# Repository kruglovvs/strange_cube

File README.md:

# strange_game
Учебный проект аппаратно-программной разработки. Представляет собой несколько плат, собираемых в куб и с напаянными различными датчиками периферии, и плату esp32 с кодом, написанным на C# nanoframework

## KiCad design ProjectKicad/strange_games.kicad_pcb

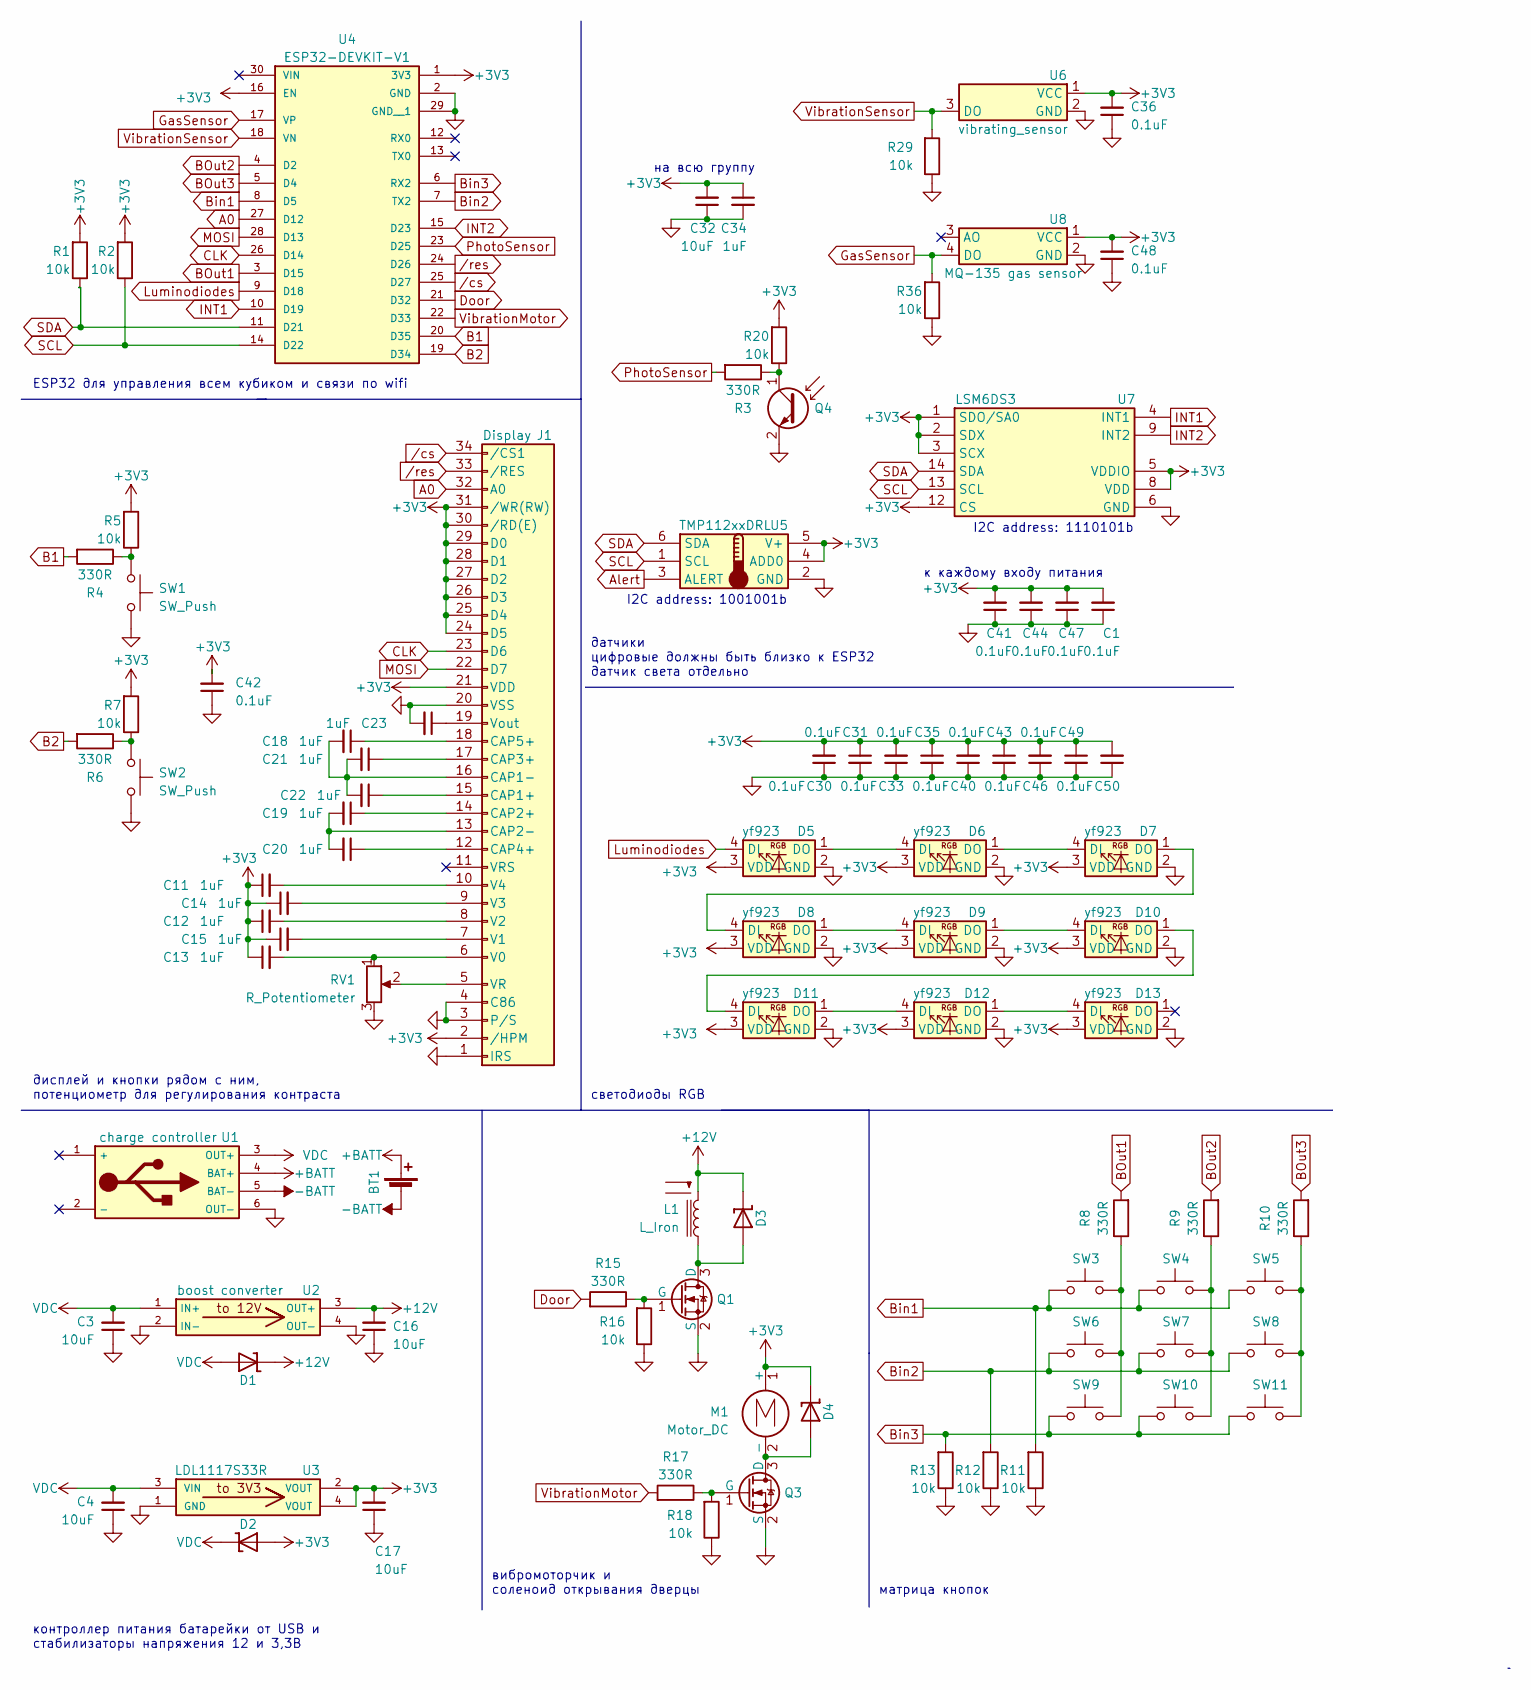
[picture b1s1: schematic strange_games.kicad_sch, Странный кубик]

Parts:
BT1: Battery_Cell; BatteryHolder_MPD_BH-18650-PC2
C1, C30, C31, C33, C35, C36, C40, C41, C42, C43, C44, C46, C47, C48, C49, C50: C_Generic; C_0402_1005Metric; Voltage 10V
C3, C4, C16, C17, C32: C_Generic; C_0805_2012Metric; Voltage 6.3V
C11, C12, C13, C14, C15, C18, C19, C20, C21, C22, C23, C34: C_Generic; C_0402_1005Metric; Voltage 16V
D1, D2, D3, D4: S07B-GS08; D_SMF
D5, D6, D7, D8, D9, D10, D11, D12, D13: yf923; library
J1: Display; TE_3-1734839-4_1x34-1MP_P0.5mm_Horizontal
L1: L_Iron; PinHeader_1x02_P2.54mm_Vertical
M1: Motor_DC; PinHeader_1x02_P2.54mm_Vertical
Q1, Q3: Si2302A; SOT-23-3; Part Number SI2318DS-T1-GE3; JLCPCB ID C14498
Q4: Q_Photo; LED_D4.0mm
R1, R2, R5, R7, R11, R12, R13, R16, R18, R20, R29, R36: 10k_0805; R_0805_2012Metric; Part Number RC0603FR-071K2L; JLCPCB ID C22765
R3, R4, R6, R8, R9, R10, R15, R17: 330_0805; R_0805_2012Metric; Part Number RC0603FR-071K2L; JLCPCB ID C22765
RV1: R_Potentiometer; TRIM_3362P-1-203LF
SW1, SW2, SW3, SW4, SW5, SW6, SW7, SW8, SW9, SW10, SW11: SW_Push; SW_PUSH-12mm
U1: charge controller; charge_controller_module_tp4056
U2: boost converter; CKCS BS-01 MT-3608 Boost Converter
U3: LDL1117S33R; SOT230P700X180-4N; Out voltage 3.3V; PARTREV 7
U4: ESP32-DEVKIT-V1; MODULE_ESP32_DEVKIT_V1; PARTREV N/A
U5: TMP112xxDRL; SOT-563
U6: vibrating_sensor; PinHeader_1x03_P2.54mm_Vertical
U7: LSM6DS3; LGA-14_3x2.5mm_P0.5mm_LayoutBorder3x4y
U8: MQ-135 gas sensor; PinHeader_1x04_P2.54mm_Vertical

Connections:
+3V3: C1.2, C11.1, C12.1, C13.1, C14.1, C15.1, C17.2, C30.2, C31.1, C32.2, C33.2, C34.1, C35.1, C36.2, C40.2, C41.2, C42.2, C43.1, C44.2, C46.2, C47.2, C48.2, C49.1, C50.2, D2.2 (A), D4.1 (K), D5.3 (VDD), D6.3 (VDD), D7.3 (VDD), D8.3 (VDD), D9.3 (VDD), D10.3 (VDD), D11.3 (VDD), D12.3 (VDD), D13.3 (VDD), J1.2 (/HPM), J1.21 (VDD), J1.24 (D5), J1.25 (D4), J1.26 (D3), J1.27 (D2), J1.28 (D1), J1.29 (D0), J1.30 (/RD(E)), J1.31 (/WR(RW)), M1.1 (+), R1.2, R2.2, R5.2, R7.2, R20.2, U3.2 (VOUT), U3.4 (VOUT), U4.1 (3V3), U4.16 (EN), U5.4 (ADD0), U5.5 (V+), U6.1 (VCC), U7.1 (SDO/SA0), U7.2 (SDX), U7.3 (SCX), U7.5 (VDDIO), U7.8 (VDD), U7.12 (CS), U8.1 (VCC)
+12V: C16.2, D1.1 (K), D3.1 (K), L1.1, U2.3 (OUT+)
+BATT: BT1.2 (+), U1.4 (BAT+)
-BATT: BT1.1 (-), U1.5 (BAT-)
A0: J1.32 (A0), U4.27 (D12)
Alert: U5.3 (ALERT)
B1: R4.2, U4.20 (D35)
B2: R6.2, U4.19 (D34)
BOut1: R8.2, U4.3 (D15)
BOut2: R9.2, U4.4 (D2)
BOut3: R10.2, U4.5 (D4)
Bin1: R11.2, SW3.1, SW4.1, SW5.1, U4.8 (D5)
Bin2: R12.2, SW6.1, SW7.1, SW8.1, U4.7 (TX2)
Bin3: R13.2, SW9.1, SW10.1, SW11.1, U4.6 (RX2)
CLK: J1.23 (D6), U4.26 (D14)
Door: R15.2, U4.21 (D32)
GND: C1.1, C3.1, C4.1, C16.1, C17.1, C23.2, C30.1, C31.2, C32.1, C33.1, C34.2, C35.2, C36.1, C40.1, C41.1, C42.1, C43.2, C44.1, C46.1, C47.1, C48.1, C49.2, C50.1, D5.2 (GND), D6.2 (GND), D7.2 (GND), D8.2 (GND), D9.2 (GND), D10.2 (GND), D11.2 (GND), D12.2 (GND), D13.2 (GND), J1.1 (IRS), J1.3 (P/S), J1.4 (C86), J1.20 (VSS), Q1.2 (S), Q3.2 (S), Q4.2 (E), R11.1, R12.1, R13.1, R16.1, R18.1, R29.1, R36.1, RV1.3, SW1.2, SW2.2, U1.6 (OUT-), U2.2 (IN-), U2.4 (OUT-), U3.1 (GND), U4.2 (GND), U4.29 (GND__1), U5.2 (GND), U6.2 (GND), U7.6 (GND), U7.7 (GND), U8.2 (GND)
GasSensor: R36.2, U4.17 (VP), U8.4 (DO)
INT1: U4.10 (D19), U7.4 (INT1)
INT2: U4.15 (D23), U7.9 (INT2)
Luminodiodes: D5.4 (DI), U4.9 (D18)
MOSI: J1.22 (D7), U4.28 (D13)
unnamed: D3.2 (A), L1.2, Q1.3 (D)
unnamed: D4.2 (A), M1.2 (-), Q3.3 (D)
unnamed: D5.1 (DO), D6.4 (DI)
unnamed: D6.1 (DO), D7.4 (DI)
unnamed: D7.1 (DO), D8.4 (DI)
unnamed: D8.1 (DO), D9.4 (DI)
unnamed: D9.1 (DO), D10.4 (DI)
unnamed: D10.1 (DO), D11.4 (DI)
unnamed: D11.1 (DO), D12.4 (DI)
unnamed: D12.1 (DO), D13.4 (DI)
unnamed: C22.1, J1.15 (CAP1+)
unnamed: C18.2, C21.2, C22.2, J1.16 (CAP1-)
unnamed: C19.1, J1.14 (CAP2+)
unnamed: C19.2, C20.2, J1.13 (CAP2-)
unnamed: C21.1, J1.17 (CAP3+)
unnamed: C20.1, J1.12 (CAP4+)
unnamed: C18.1, J1.18 (CAP5+)
unnamed: C13.2, J1.6 (V0), RV1.1
unnamed: C15.2, J1.7 (V1)
unnamed: C12.2, J1.8 (V2)
unnamed: C14.2, J1.9 (V3)
unnamed: C11.2, J1.10 (V4)
unnamed: J1.5 (VR), RV1.2
unnamed: C23.1, J1.19 (Vout)
unnamed: Q1.1 (G), R15.1, R16.2
unnamed: Q3.1 (G), R17.1, R18.2
unnamed: Q4.1 (C), R3.1, R20.1
unnamed: R4.1, R5.1, SW1.1
unnamed: R6.1, R7.1, SW2.1
unnamed: R8.1, SW3.2, SW6.2, SW9.2
unnamed: R9.1, SW4.2, SW7.2, SW10.2
unnamed: R10.1, SW5.2, SW8.2, SW11.2
PhotoSensor: R3.2, U4.23 (D25)
SCL: R2.1, U4.14 (D22), U5.1 (SCL), U7.13 (SCL)
SDA: R1.1, U4.11 (D21), U5.6 (SDA), U7.14 (SDA)
VDC: C3.2, C4.2, D1.2 (A), D2.1 (K), U1.3 (OUT+), U2.1 (IN+), U3.3 (VIN)
VibrationMotor: R17.2, U4.22 (D33)
VibrationSensor: R29.2, U4.18 (VN), U6.3 (DO)
/cs: J1.34 (/CS1), U4.25 (D27)
/res: J1.33 (/RES), U4.24 (D26)

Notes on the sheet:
к каждому входу питания
светодиоды RGB
ESP32 для управления всем кубиком и связи по wifi
матрица кнопок
вибромоторчик и соленоид открывания дверцы
дисплей и кнопки рядом с ним, потенциометр для регулирования контраста
на всю группу
I2C address: 1001001b
датчики цифровые должны быть близко к ESP32 датчик света отдельно
I2C address: 1110101b
контроллер питания батарейки от USB и стабилизаторы напряжения 12 и 3,3В

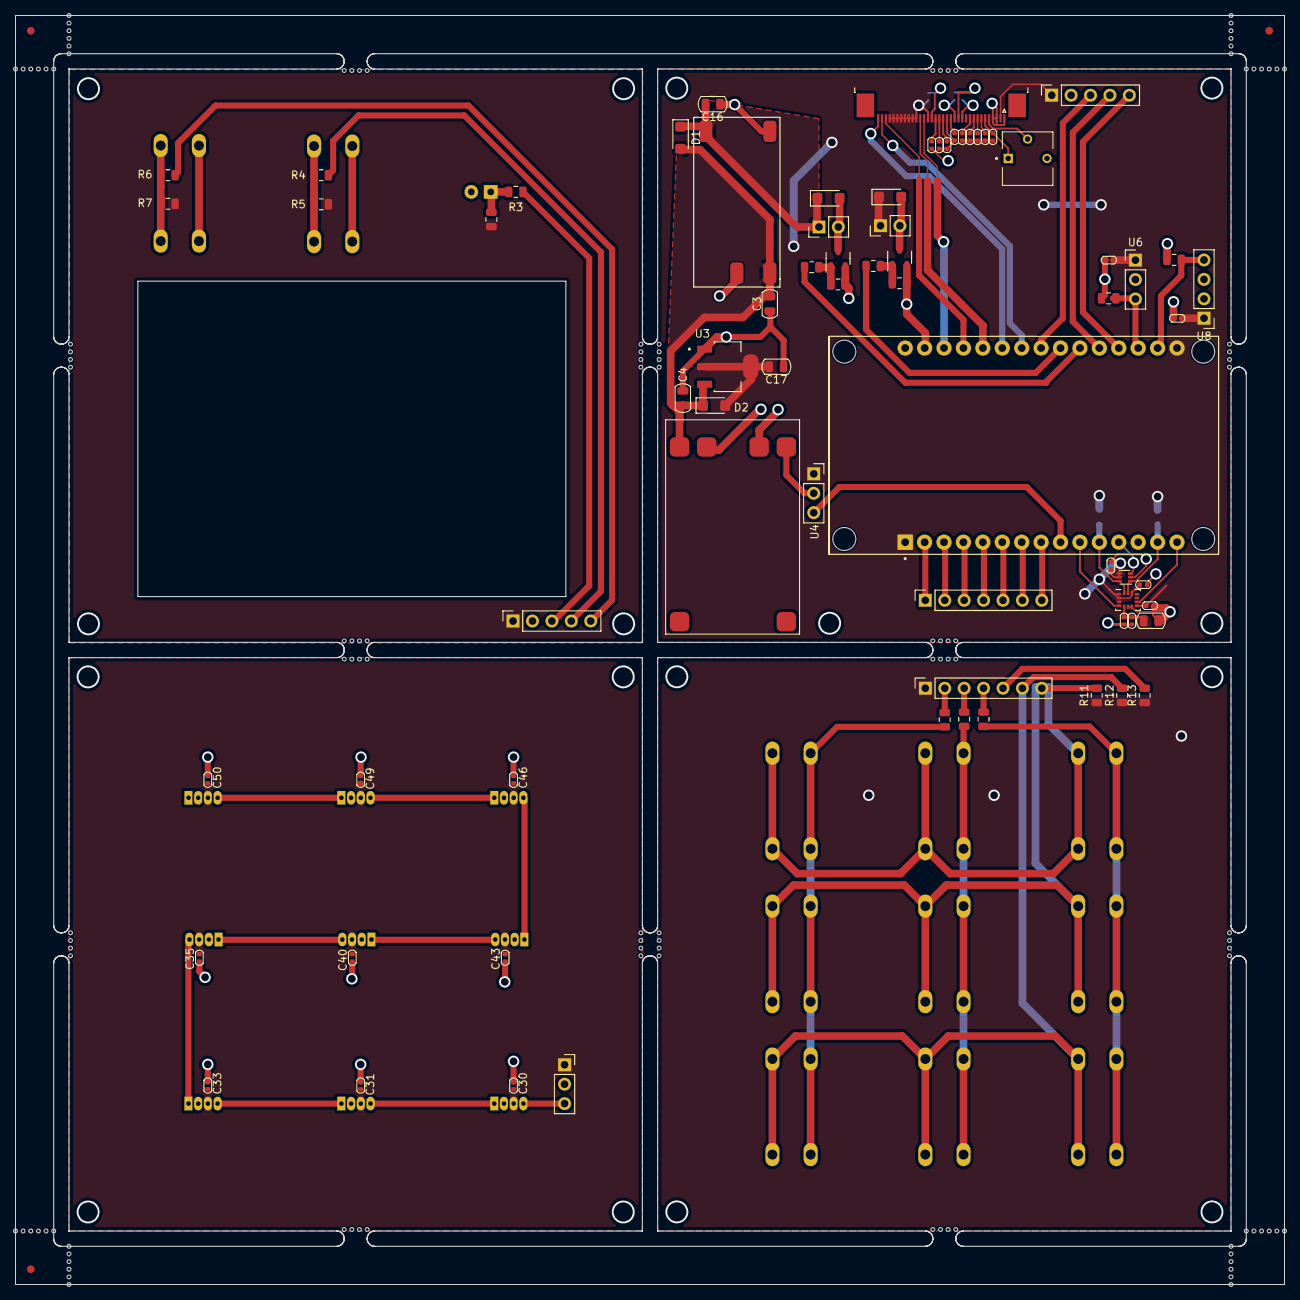
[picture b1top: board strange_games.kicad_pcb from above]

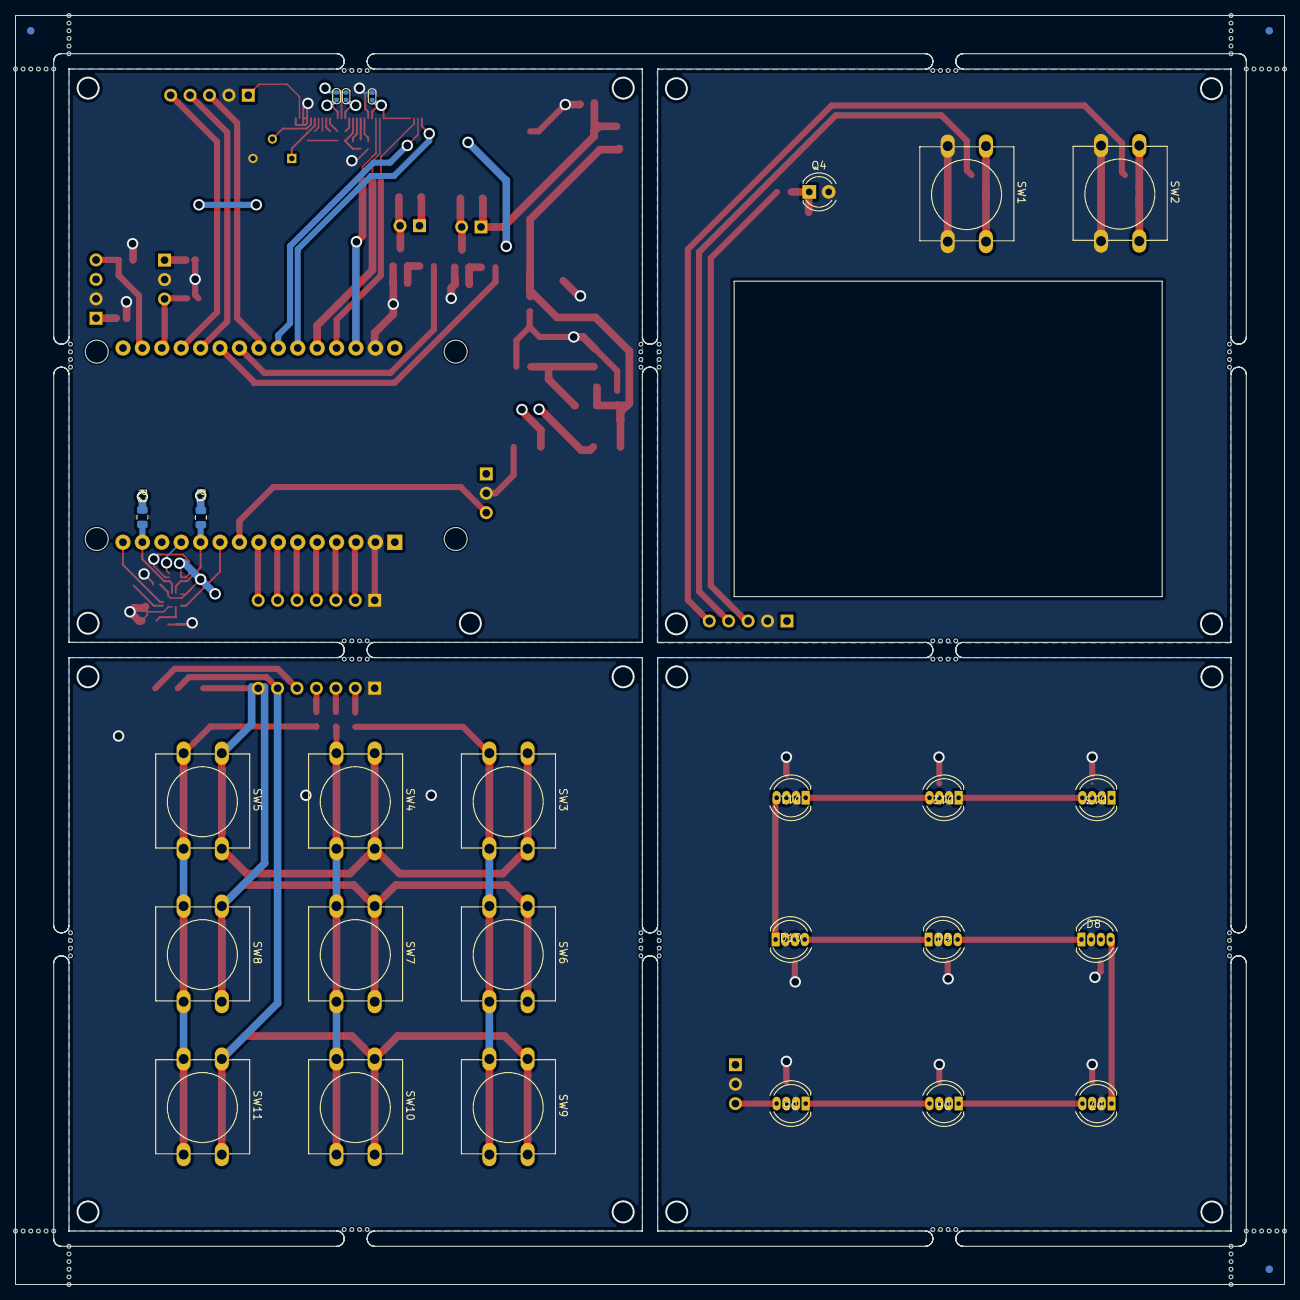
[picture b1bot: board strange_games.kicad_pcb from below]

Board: 2 copper layers, 166.0 x 166.0 mm, 92 parts (26 on the bottom side), 59 nets.

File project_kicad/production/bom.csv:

Designator,Footprint,Quantity,Value,LCSC Part #
"C1, C11, C12, C13, C14, C15, C18, C19, C20, C21, C22, C23, C30, C31, C33, C34, C35, C36, C40, C41, C42, C43, C44, C46, C47, C48, C49, C50",0402,28,C_Generic,
"C16, C17, C3, C32, C4",0805,5,C_Generic,
"D1, D2, D3, D4",D_SMF,4,S07B-GS08,
"D10, D11, D12, D13, D5, D6, D7, D8, D9",LED_D5.0mm-4_RGB,9,yf923,
J1,TE_3-1734839-4_1x34-1MP_P0.5mm_Horizontal,1,Display,
L1,PinHeader_1x02_P2.54mm_Vertical,1,L_Iron,
M1,PinHeader_1x02_P2.54mm_Vertical,1,Motor_DC,
"Q1, Q3",SOT-23-3,2,Si2302A,
Q4,LED_D4.0mm,1,Q_Photo,
"R1, R11, R12, R13, R16, R18, R2, R20, R29, R36, R5, R7",0805,12,10k_0805,
"R10, R15, R17, R3, R4, R6, R8, R9",0805,8,330_0805,
RV1,TRIM_3362P-1-203LF,1,R_Potentiometer,
"SW1, SW10, SW11, SW2, SW3, SW4, SW5, SW6, SW7, SW8, SW9",SW_PUSH-12mm,11,SW_Push,
U1,charge_controller_module_tp4056,1,charge controller,
U2,CKCS BS-01 MT-3608 Boost Converter,1,boost converter,
U3,SOT230P700X180-4N,1,LDL1117S33R,
U4,MODULE_ESP32_DEVKIT_V1,1,ESP32-DEVKIT-V1,
U5,SOT-563,1,TMP112xxDRL,
U6,PinHeader_1x03_P2.54mm_Vertical,1,vibrating_sensor,
U7,LGA-14_3x2.5mm_P0.5mm_LayoutBorder3x4y,1,LSM6DS3,
U8,PinHeader_1x04_P2.54mm_Vertical,1,MQ-135 gas sensor,

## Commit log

2023-06-07 made folders
    added some submodules and made folders for out code of stm32 and esp8266
2023-06-07 added submodule tmp112
    added one more submodule for tmp112
2023-06-07 rewrite submodule file
    rewrite submodule file
2023-06-22 made schematic
    I Made schematic and started making pcb. The next step is to make pcb
2023-06-22 remade phototransistors
    remade phototransistors, replaced it with resistor. Need to update pins in sch
2023-06-23 unziped project
2023-06-27 replaces stm32 with esp32
    remade schematic, replacing stm32 with esp32, starting making pcb. Deleted projects for stm32 and esp8266
2023-06-27 updated components numbers
2023-06-27 deleted pins
    deleted temperature alert pin and 2 buttons near the display because there are no enough pins in esp32
2023-06-28 some more changes in sch
2023-06-28 updated placements for pcb
2023-06-28 pcb changes
2023-06-28 created esp32 project
    we are going to programe esp32 with C# nanoframework with cisual studio because I just want to learn C#
2023-06-28 updated buttons
2023-06-29 updated pcb
2023-06-30 code changes
2023-07-01 changed 10kR to 330R
2023-07-02 remastered display pins in the kicad scheme
2023-07-02 made data class
2023-07-02 pcb updates
2023-07-02 pcb changes
    deleted resistor from unused pins because they take so much place
2023-07-03 c# updates
2023-07-03 made classes for periphery
2023-07-04 making i2c connections
2023-07-04 pcb update
2023-07-05 made pcb
2023-07-05 made i2c
2023-07-06 code update and pcb remade a0 track
2023-07-06 using
2023-07-10 creating display
2023-07-10 pcb changes deleted 1 button and made /res pin
2023-07-10 remastered network.cs
2023-07-10 remastered with interfaces
2023-07-11 pcb changes
    Remade traces: now the are 1mm wide
2023-07-11 I need to remaster everything
2023-07-11 Network is ready and should be tested
2023-07-12 bugfix
    In the last version we lost netlist - it was improved
2023-07-12 kicad changes + trash esp32
    made via's better to make it possible to create
2023-07-12 It should be remastered with events
2023-07-14 remastered network with events
2023-07-14 I need to turn off displays and etc. It should be remade with functions
2023-07-19 The great remaster
    Remade code, split it to folders
2023-07-20 made it possible to open and remastered static classes
    I have not enough memory to use this code... I need to make it less weight
2023-07-20 I need new remaster: delete all this shit and make it simple
    remade main
2023-07-20 remastered code
    Made 3 big files., removed events, made delegates for regular events from nanoframework. I Believe esp32 has enough for this shit
2023-07-22 Made it working
    I found that there was a recurtion in set blocks. I think that it is possible to return the previous code
2023-07-24 trying to interop
2023-07-26 started returning the prev. code style
2023-07-26 Remastered network and periphery for the prev codestyle
2023-07-27 Made it?
2023-07-27 uncommented network connections
2023-08-30 forget to add
